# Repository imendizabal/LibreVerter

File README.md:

# Aim of the project
LibreVerter - An open inverter, built for a lifetime. 
A home inverter, to interface battery systems and PV systems with the UK and EU electricity grids.

The LibreVerter will be:
- Durable
- Repairable
- Open-Source

The main goal of the project is to develop an open source inverter (Hardware and Software)  
The initial configuration of the project will be a single phase, 2 kW inverter

An important part of the project is to be able to work with different types of switching components (IGBT/MOSFET). Nowadays, we often see that inverters are replaced after 10 years but they keep working or some faulty inverters that are not easily repared because the design is not modular or easy to fix.

Then, the goal is to design an Open Source inverter that is modular to be easy to be fixed and flexible enough to have differents functionalities (batteries/PV/...)

The project will be divided into different "workpackages" based on the functional blocks needed to make the whole system work. These functional blocks are called "Modules", and may be split into further modules where necessary. The diagram below shows the module definitions we are currently working to. 

1. Supervisory control: development of the main control board able to get the measurements, generate references, ... This board embeds the main mcu.
2. Inverter Board.
3. DC/DC converter: Able to take a variable DC input (48V +/- 20%) and output a stable DC output controllable between 360 V and 500 V.
4. DC Link: A DC link capable of self-protection.
5. A DC filter for smooth input/output.
6. DC Protections for over-current, over-voltage protection and under-voltage protection. 
7. DC connections for physically connecting the DC source to LibreVerter.
8. Maximum Power Point Tracker DC/DC converter for connecting the solar panels to LibreVerter and extracting the maximum power.
9.  AC filter for smooth sine wave input/output.
10. AC protection for over-current and over-voltage protection. Required for compatibility with grid codes.
11. Connections for phsyically conecting the external electrical system to LibreVerter.
12. Human Machine Interface (HMI) to act as the interface between the user and the supervisory control

For the Inverter board, two sub-modules are assumed:
1. Control and Driver board: interface between the supervisory control board and power switch (IGBT's/Mosfet's). The driver board needs to generate the PWM signals based on a reference from the supervisor.
2. Power circuit: power circuit of the inverter

# Who are we making this for?
Our ideal customer profile is:
A “solar as a service” provider. Responsible for through life maintenance. Because:
1. They are able to buy LibreVerters via individual customer orders.
2. Their interests are aligned with selling as many systems as possible, as well as being able to maintain the systems at low cost. Repair and re-use are essential.
3. They are regularly buying inverter systems.
4. They are likely to be a relatively small company, maybe 10-50 people, with big buying power via their customers.

We are also interested in serving other customers who want an inverter for life; we'd love to hear from you if you fit that description! 

# Expected functionalities

- Being able (and allowed) to be connected to the European grid
- MPPT for solar panels (with DC/DC)
- Battery connection
- Communication capabilities (serial,...)
- Working in islanding mode (offgrid)

# 1. Supervisory control board:

For the supervisory control, the firmware on the main mcu should have (main mcu based on STM32G434):

1. Low level drivers
2. Basics functionalities (bootloader, debug uart, pll,...)
3. Advanced functionalities (power management, MPPT, state machine)

The main control board will be able to measure:
1.  3AC voltages (max 400V) - ADC min 14bits
2.  2DC voltages (max 1500V) -ADC min 14bits
3.  4AC/DC current measurement - ADC min 14bits
4.  Temperature measurement

The main control board will have the following interface:
1.  2X UART(1X to RS485; 1X to USB)
2.  1xSPI
3.  2xI2C
4.  1xCAN
5.  6X PWM's
6.  6X DO's
7.  6X DI's
8.  6X AI'S (temp from IGBT/Mos)

Other functions:
1.  Debug LED
2.  RTC (supercap based)
3.  Additionnal ROM (TBD)
4.  Watchdog
5.  Power supply for IGBT's/Mosfets

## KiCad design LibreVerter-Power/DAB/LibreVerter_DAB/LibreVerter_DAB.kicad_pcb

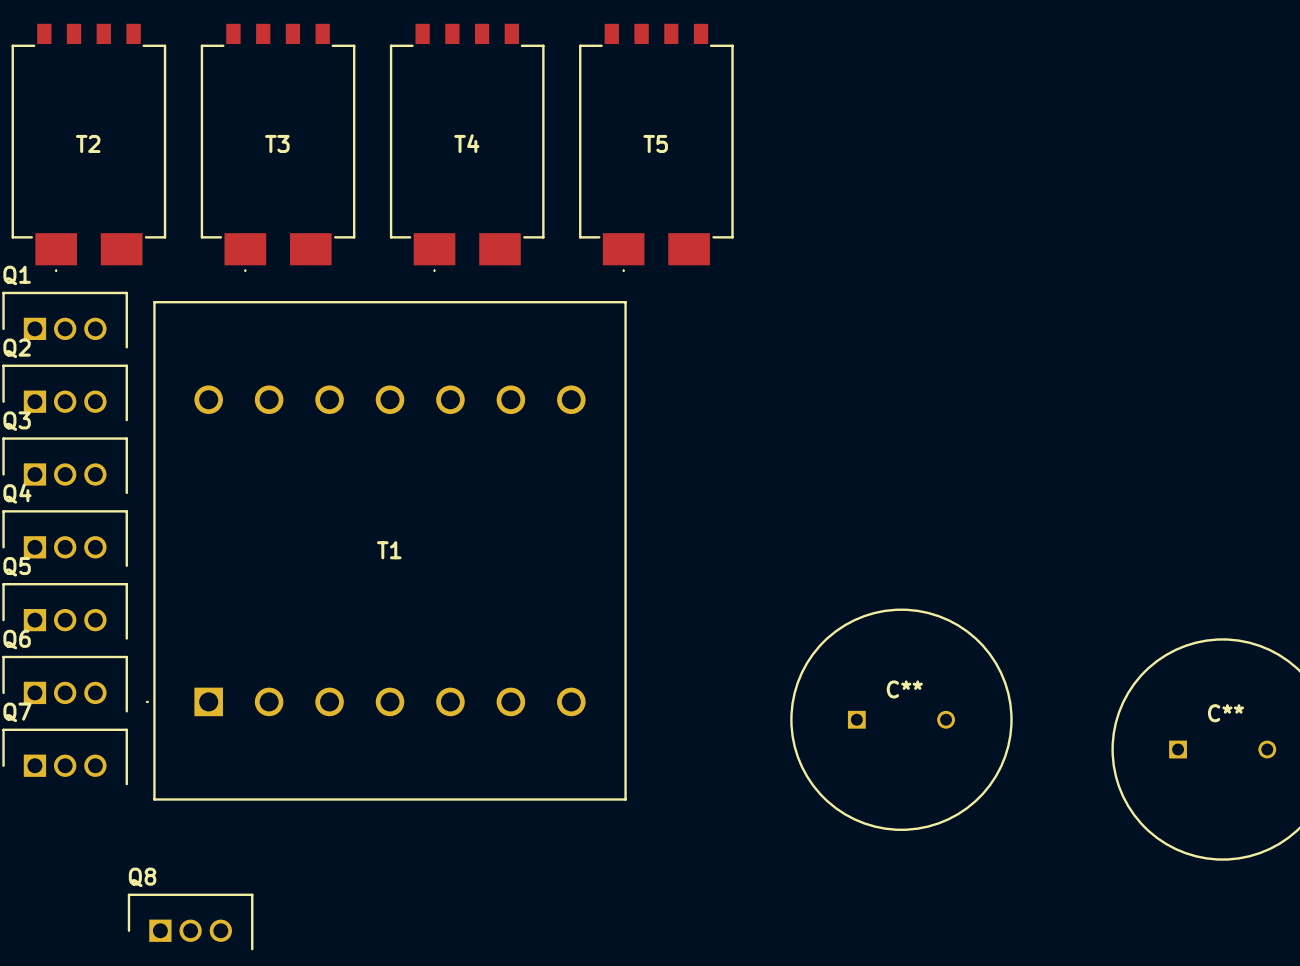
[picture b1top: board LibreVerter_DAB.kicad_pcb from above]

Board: 2 copper layers, 15 parts (0 on the bottom side), 11 nets, no tracks yet.

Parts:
C**: CAPPRD750W80D1850H4200
C**#2: CAPPRD750W80D1850H4200
Q1, Q2, Q3, Q4: IPP023N10N5XKSA1; TO254P457X1003X2115-3P
Q5, Q6, Q7, Q8: IPP60R060P7XKSA1; TO254P457X1003X2115-3P
T1: B66362W1014T001
T2, T3, T4, T5: PAS6322.150NLT; PAS6322150NLT

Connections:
GND: T2.2 (PRI_50KHZ-1MHZ), T5.2 (PRI_50KHZ-1MHZ)
GND2: T3.2 (PRI_50KHZ-1MHZ), T4.2 (PRI_50KHZ-1MHZ)
unnamed: Q1.2 (D), Q3.2 (D)
unnamed: Q1.3 (S), Q2.2 (D), T1.1, T1.2, T1.3
unnamed: Q2.3 (S), T5.1 (PRI_50KHZ-1MHZ)
unnamed: Q3.3 (S), Q4.2 (D), T1.5, T1.6, T1.7
unnamed: Q4.3 (S), T2.1 (PRI_50KHZ-1MHZ)
unnamed: Q5.3 (S), Q6.2 (D), T1.12, T1.13, T1.14
unnamed: Q6.3 (S), T3.1 (PRI_50KHZ-1MHZ)
unnamed: Q7.3 (S), Q8.2 (D), T1.8, T1.9, T1.10
unnamed: Q8.3 (S), T4.1 (PRI_50KHZ-1MHZ)

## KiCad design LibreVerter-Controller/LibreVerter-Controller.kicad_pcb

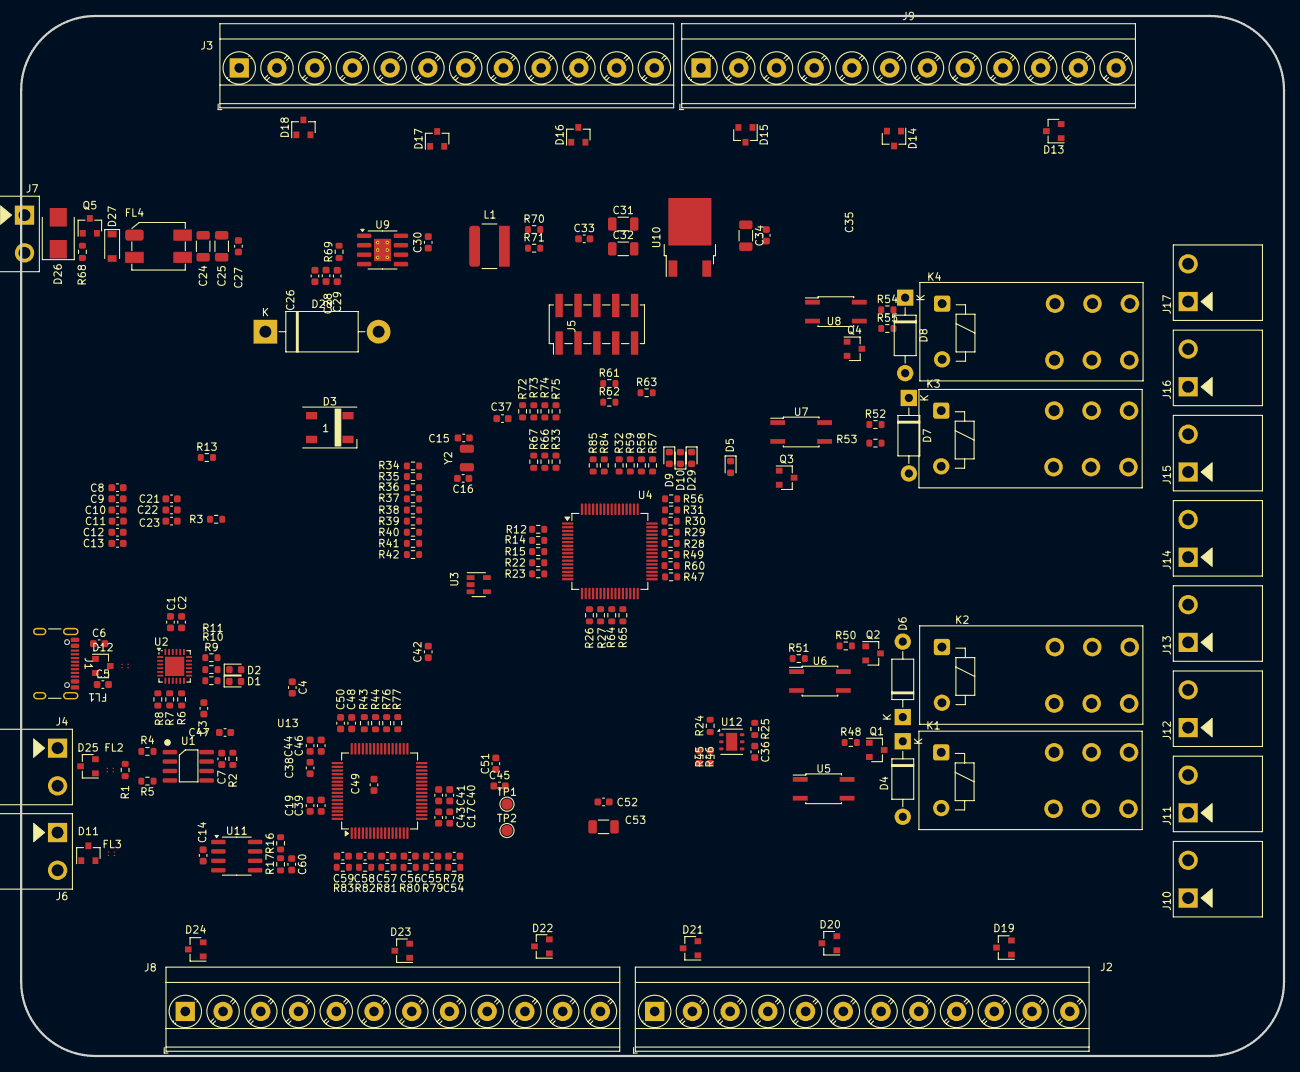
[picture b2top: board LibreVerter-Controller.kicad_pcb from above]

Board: 2 copper layers, 170.0 x 140.0 mm, 215 parts (0 on the bottom side), 174 nets, no tracks yet.

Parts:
C1, C3, C5, C7, C8, C10, C11, C12, C13, C14, C21, C22, C23, C27, C30, C33, C35, C36, C37, C39, C41, C43, C46, C49, C50, C52: 100nF; C_0603_1608Metric
C2, C4, C6, C17, C19, C38, C40, C42, C44, C45, C47, C48, C51: 1uF; C_0603_1608Metric
C9: 10nF; C_0603_1608Metric
C15, C16: 9pF; C_0603_1608Metric
C24, C25: 10uF; C_1206_3216Metric
C26: 22nF; C_0603_1608Metric
C28: 47pF; C_0603_1608Metric
C29, C60: 4.7nF; C_0603_1608Metric
C31, C32, C34: 47uF; C_1206_3216Metric
C53: 22uF; C_1206_3216Metric
C54, C55, C56, C57, C58, C59: 1nF; C_0603_1608Metric
D1, D2: LED_Small; LED_0603_1608Metric
D3: WS2812B; LED_WS2812B_PLCC4_5.0x5.0mm_P3.2mm
D4, D6, D7, D8: 1N47xxA; D_DO-41_SOD81_P10.16mm_Horizontal
D5, D9, D10, D29: 150060RS55040; LED_0603_1608Metric
D11, D25: TVS_2-Channel-7V; SOT-23
D12: 824022; SOT-23
D13, D14, D15, D16, D17, D18, D19, D20, D21, D22, D23, D24: PESD3V3L2BT; SOT-23
D26: SMBJ30CA; D_SMB
D27: Zener_6V; D_SOD-123
D28: 1N5820; D_DO-201AD_P15.24mm_Horizontal
FL1, FL2, FL3: TCM0403M-350-2P-T210; Choke_TDK_TCM0403M-350-2P-T210
FL4: ACM7060-701-2PL-TL01; ChokeSMD_ACM7060
J1: USB_C_Receptacle_USB2.0; USB_C_Receptacle_GCT_USB4105-xx-A_16P_TopMnt_Horizontal
J2, J3, J8, J9: TerminalBlock_1x12; TerminalBlock_Phoenix_MKDS-3-12-5.08_1x12_P5.08mm_Horizontal
J4, J6, J7, J10, J11, J12, J13, J14, J15, J16, J17: 1x02; WURTH-691312510002
J5: Conn_ARM_JTAG_SWD_10; PinHeader_2x05_P2.54mm_Vertical_SMD
K1, K2, K3, K4: RZH3-1C4-D012; Relay_TE_RZH3-1C04-D012
L1: 10μH-5A; Inductor_Wurth_XHMI-6060
Q1, Q2, Q3, Q4: MMSS8050-H-TP; SOT-23
Q5: SI2347DS-T1-GE3; SOT-23
R1, R48, R49, R50, R51, R52, R53, R54, R55, R72, R73, R74: 120Ω; R_0603_1608Metric
R2, R3, R45, R46: 0; R_0603_1608Metric
R4, R5, R14, R15, R22, R23, R26, R27, R28, R29, R30, R31, R32, R33, R34, R35, R36, R37, R38, R39, R40, R41, R42, R47, R56, R57, R58, R59, R60, R61, R62, R63, R64, R65, R66, R67, R84, R85: 100; R_0603_1608Metric
R6: 22K1; R_0603_1608Metric
R7: 47K5; R_0603_1608Metric
R8, R78, R79, R80, R81, R82, R83: 1K; R_0603_1608Metric
R9, R10: 470Ω; R_0603_1608Metric
R11, R13, R43, R44, R76, R77: 10KΩ; R_0603_1608Metric
R12, R24, R25: 4K7; R_0603_1608Metric
R16, R17: 60Ω; R_0603_1608Metric
R68: 12K; R_0603_1608Metric
R69: 49.9; R_0603_1608Metric
R70: 43KΩ; R_0603_1608Metric
R71: 8.2KΩ; R_0603_1608Metric
R75: 330; R_0603_1608Metric
TP1, TP2: TestPoint_1.5mm; TestPoint_Pad_D1.5mm
U1: SP3485EN; SOIC-8_3.9x4.9mm_P1.27mm
U2: CP2102N-A02-GQFN24; QFN-24-1EP_4x4mm_P0.5mm_EP2.6x2.6mm
U3: STWD100; SOT-23-5
U4, U13: LQFP-64_10x10mm_P0.5mm
U5, U6, U7, U8: LTV-356T; SO-4_4.4x3.6mm_P2.54mm
U9: TPS54331DR; SOIC-8-1EP_3.9x4.9mm_P1.27mm_EP2.29x3mm_ThermalVias
U10: BD33FC0FP-E2; TO-252-2
U11: ATA6560; SOIC-8_3.9x4.9mm_P1.27mm
U12: HDC2080; Texas_PWSON-N6
Y2: Crystal; Oscillator_SMD_ECS_2520MV-xxx-xx-4Pin_2.5x2.0mm

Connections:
+3V3: C1.1, C2.1, C8.1, C11.1, C12.1, C13.1, C14.1, C21.1, C22.1, C23.1, C34.1, C35.1, C36.1, C44.1, C46.1, C48.1, C50.1, D1.2 (K), D2.2 (K), J5.1 (VTref), R2.1, R8.1, R13.2, R24.2, R25.1, R45.1, R74.1, U2.5 (VIO), U2.6 (VDD), U2.7 (VREGIN), U3.5 (VCC), U4.16 (VDD), U4.29 (VDDA), U4.32 (VDD), U4.48 (VDD), U4.64 (VDD), U10.3 (Vout), U11.3 (VCC), U12.5 (VDD), U13.48 (DVDD), U13.50 (DVDD)
+5V: C17.1, C19.1, C31.1, C32.1, C33.1, C37.1, C38.1, C39.1, C40.1, C41.1, C42.1, C43.1, D3.4 (VDD), L1.2, R3.1, R70.1, R75.1, U10.1 (Vin), U13.19 (AVDD), U13.21 (AVDD), U13.22 (AVDD), U13.54 (AVDD1), U13.56 (AVDD), U13.59 (AVDD)
+BATT: C10.1, U4.1 (VBAT)
/CAN_N: FL3.4, R17.2, U11.6 (CANL)
/CAN_P: FL3.2, R16.1, U11.7 (CANH)
/Dry Contact_1/DRY1_C: J11.2, K1.12
/Dry Contact_1/DRY1_O: J11.1, K1.14
/Dry Contact_1/DRY_CONT: J10.2, K1.11
/Dry Contact_1/DRY_V: D4.1 (K), J10.1, K1.A2, U5.4
/Dry Contact_2/DRY1_C: J12.2, K2.12
/Dry Contact_2/DRY1_O: J12.1, K2.14
/Dry Contact_2/DRY_CONT: J13.2, K2.11
/Dry Contact_2/DRY_V: D6.1 (K), J13.1, K2.A2, U6.4
/Dry Contact_3/DRY1_C: J15.2, K3.12
/Dry Contact_3/DRY1_O: J15.1, K3.14
/Dry Contact_3/DRY_CONT: J14.2, K3.11
/Dry Contact_3/DRY_V: D7.1 (K), J14.1, K3.A2, U7.4
/Dry Contact_4/DRY1_C: J17.2, K4.12
/Dry Contact_4/DRY1_O: J17.1, K4.14
/Dry Contact_4/DRY_CONT: J16.2, K4.11
/Dry Contact_4/DRY_V: D8.1 (K), J16.1, K4.A2, U8.4
/EXT_CAN_N: D11.2, FL3.3, J6.2
/EXT_CAN_P: D11.1, FL3.1, J6.1
/IN_AN1: D24.3, J8.1, R78.1
/IN_AN2: D24.1, J8.3, R79.1
/IN_AN3: D19.1, D23.3, J2.12 (Pin_8), J8.5, R33.1, R80.1
/IN_AN4: D23.1, J8.7 (Pin_10), R81.1
/IN_AN5: D22.3, J8.9 (Pin_12), R82.1
/IN_AN6: D22.1, J8.12 (Pin_8), R83.1
/IN_DIG1: D21.3, J2.1, R28.1
/IN_DIG2: D21.1, J2.3, R29.1
/IN_DIG3: D20.3, J2.5, R30.1
/IN_DIG4: D20.1, J2.7 (Pin_10), R31.1
/IN_DIG5: D19.3, J2.9 (Pin_12), R32.1
/JTCK: J5.4 (SWDCLK/TCK), R58.1
/JTDI: J5.8 (NC/TDI), R59.1
/JTDO: J5.6 (SWO/TDO), R66.2, R67.2
/JTMS: J5.2 (SWDIO/TMS), R57.1
/MCU/CAN_NSIL: R85.2, U11.5 (NSIL)
/MCU/CAN_STBY: R84.2, U11.8 (STBY)
/MCU/LED1: R72.1, U4.55 (PD2)
/MCU/LED2: R73.1, U4.30 (PB10)
/MCU/MCU_RST: C9.2, R12.2, R13.1, U4.7 (NRST)
/MCU/RS485: U1.2 (~RE), U1.3 (DE), U2.12 (RS485/IO2)
/MCU/RX0_3V3: R4.1, U2.21 (TXD)
/MCU/SCL: R25.2, U12.6 (SCL)
/MCU/SDA: R24.1, U12.1 (SDA)
/MCU/TX0_3V3: R5.1, U2.20 (RXD)
/MCU/VCAP2: C51.1, C52.1, U13.30 (VCAP2)
/MCU/VCAP3: C47.1, C49.1, U13.55 (VCAP3)
/MCU/VCAP4: C45.1, U13.26 (VCAP4)
/OUT_DIG1: D18.3, J3.1, R14.1
/OUT_DIG2: D18.1, J3.3, R15.1
/OUT_DIG3: D17.3, J3.5, R22.1
/OUT_DIG4: D17.1, J3.7 (Pin_10), R23.1
/OUT_DIG5: D16.3, J3.9 (Pin_12), R26.1
/OUT_DIG6: D16.1, J3.12 (Pin_8), R27.1
/OUT_DRY1: R49.2, R60.2
/OUT_DRY2: R51.2, R61.2
/OUT_DRY3: R53.2, R62.2
/OUT_DRY4: R55.2, R63.2
/OUT_PWM1: D15.3, J9.1, R34.1
/OUT_PWM2: D15.1, J9.3, R35.1
/OUT_PWM3: D14.3, J9.5, R36.1
/OUT_PWM4: D14.1, J9.7 (Pin_10), R37.1
/OUT_PWM5: D13.3, J9.9 (Pin_12), R38.1
/OUT_PWM6: D13.1, J9.12 (Pin_8), R56.1
/RS485_EXT_N: D25.1, FL2.3, J4.2
/RS485_EXT_P: D25.2, FL2.1, J4.1
/RS485_N: FL2.4, R1.2, U1.7 (B)
/RS485_P: FL2.2, R1.1, U1.6 (A)
/USB_D_N: FL1.4, U2.4 (D-)
/USB_D_P: FL1.2, U2.3 (D+)
/USB_IN_N: D12.1 (IO1), FL1.3, J1.A6 (D+), J1.B6 (D+)
/USB_IN_P: D12.3 (IO2), FL1.1, J1.A7 (D-), J1.B7 (D-)
GND: C1.2, C2.2, C3.2, C4.2, C5.2, C6.2, C7.2, C8.2, C9.1, C10.2, C11.2, C12.2, C13.2, C14.2, C15.2, C16.2, C17.2, C19.2, C21.2, C22.2, C23.2, C26.2, C28.2, C31.2, C32.2, C33.2, C34.2, C35.2, C36.2, C37.2, C38.2, C39.2, C40.2, C41.2, C42.2, C43.2, C44.2, C45.2, C46.2, C47.2, C48.2, C49.2, C50.2, C51.2, C52.2, C53.2, C54.2, C55.2, C56.2, C57.2, C58.2, C59.2, C60.1, D3.2 (GND), D5.2 (K), D9.2 (K), D10.2 (K), D11.3, D12.2 (GND), D13.2, D14.2, D15.2, D16.2, D17.2, D18.2, D19.2, D20.2, D21.2, D22.2, D23.2, D24.2, D25.3, D28.2 (A), D29.2 (K), J1.A1 (GND), J1.A12 (GND), J1.B1 (GND), J1.B12 (GND), J1.S1 (SHIELD), J2.2, J2.4, J2.6, J2.8 (Pin_11), J2.10 (Pin_13), J2.11 (Pin_7), J3.2, J3.4, J3.6, J3.8 (Pin_11), J3.10 (Pin_13), J3.11 (Pin_7), J5.3 (GND), J5.5 (GND), J5.9 (GNDDetect), J8.2, J8.4, J8.6, J8.8 (Pin_11), J8.10 (Pin_13), J8.11 (Pin_7), J9.2, J9.4, J9.6, J9.8 (Pin_11), J9.10 (Pin_13), J9.11 (Pin_7), R7.2, R11.2, R43.2, R44.2, R46.2, R69.2, R71.2, R76.2, R77.2, U1.5 (GND), U2.2 (GND), U2.25 (GND), U3.2 (GND), U4.15 (VSS), U4.27 (VSSA), U4.31 (VSS), U4.47 (VSS), U4.63 (VSS), U5.2, U6.2, U7.2, U8.2, U9.7 (GND), U9.9 (PAD), U10.2 (GND), U11.2 (GND), U12.2 (GND), U13.1 (IN8N), U13.2 (IN8P), U13.3 (IN7N), U13.4 (IN7P), U13.5 (IN6N), U13.7 (IN5N), U13.9 (IN4N), U13.11 (IN3N), U13.13 (IN2N), U13.15 (IN1N), U13.20 (AVSS), U13.23 (AVSS), U13.27 (REFN), U13.32 (AVSS), U13.33 (DGND), U13.49 (DGND), U13.51 (DGND), U13.53 (AVSS1), U13.57 (AVSS), U13.58 (AVSS)
GND1: Q1.2 (E), Q2.2 (E), Q3.2 (E), Q4.2 (E)
unnamed: C24.2, C25.2, C27.2, FL4.3
unnamed: C29.2, R69.1
unnamed: C60.2, R16.2, R17.1
unnamed: D1.1 (A), R9.2
unnamed: D2.1 (A), R10.2
unnamed: D4.2 (A), K1.A1, Q1.3 (C)
unnamed: D5.1 (A), R72.2
unnamed: D6.2 (A), K2.A1, Q2.3 (C)
unnamed: D7.2 (A), K3.A1, Q3.3 (C)
unnamed: D8.2 (A), K4.A1, Q4.3 (C)
unnamed: D9.1 (A), R73.2
unnamed: D10.1 (A), R74.2
unnamed: D26.1 (A1), FL4.2, J7.2, R68.1
unnamed: D26.2 (A2), J7.1, Q5.3 (D)
unnamed: D27.2 (A), Q5.1 (G), R68.2
unnamed: D27.1 (K), FL4.1, Q5.2 (S)
unnamed: C30.2, D28.1 (K), L1.1, U9.8 (PH)
unnamed: D29.1 (A), R75.2
unnamed: Q1.1 (B), R48.1
unnamed: Q2.1 (B), R50.1
unnamed: Q3.1 (B), R52.1
unnamed: Q4.1 (B), R54.1
unnamed: R48.2, U5.3
unnamed: R49.1, U5.1
unnamed: R50.2, U6.3
unnamed: R51.1, U6.1
unnamed: R52.2, U7.3
unnamed: R53.1, U7.1
unnamed: R54.2, U8.3
unnamed: R55.1, U8.1
unnamed: R5.2, U1.4 (DI)
unnamed: R4.2, U1.1 (RO)
unnamed: C7.1, R2.2, R3.2, U1.8 (VCC)
unnamed: R9.1, U2.13 (RXT/IO1)
unnamed: R10.1, U2.14 (TXT/IO0)
unnamed: R6.2, R7.1, U2.8 (VBUS)
unnamed: R8.2, U2.9 (~RST)
unnamed: R11.1, U2.15 (~SUSPEND)
unnamed: R12.1, U3.1 (~WDO)
unnamed: C16.1, U4.3 (OSC32_IN), Y2.1
unnamed: C15.1, U4.4 (OSC32_OUT), Y2.2
unnamed: R34.2, U4.12 (PA0)
unnamed: R35.2, U4.13 (PA1)
unnamed: R36.2, U4.14 (PA2)
unnamed: R37.2, U4.17 (PA3)
unnamed: R38.2, U4.18 (PA4)
unnamed: R39.2, U4.19 (PA5)
unnamed: R40.2, U4.20 (PA6)
unnamed: R41.2, U4.21 (PA7)
unnamed: R42.2, U4.42 (PA8)
unnamed: R47.2, U4.43 (PA9)
unnamed: R56.2, U4.46 (PA12)
unnamed: R57.2, U4.49 (PA13)
unnamed: R58.2, U4.50 (PA14)
unnamed: R59.2, U4.51 (PA15)
unnamed: R64.1, U4.24 (PB0)
unnamed: R65.1, U4.25 (PB1)
unnamed: R66.1, U4.56 (PB3)
unnamed: R67.1, U4.57 (PB4)
unnamed: R84.1, U4.58 (PB5)
unnamed: R85.1, U4.59 (PB6)
unnamed: R60.1, U4.33 (PB11)
unnamed: R61.1, U4.34 (PB12)
unnamed: R62.1, U4.35 (PB13)
unnamed: R63.1, U4.36 (PB14)
unnamed: R14.2, U4.8 (PC0)
unnamed: R15.2, U4.9 (PC1)
unnamed: R22.2, U4.10 (PC2)
unnamed: R23.2, U4.11 (PC3)
unnamed: R26.2, U4.22 (PC4)
unnamed: R27.2, U4.23 (PC5)
unnamed: R28.2, U4.38 (PC6)
unnamed: R29.2, U4.39 (PC7)
unnamed: R30.2, U4.40 (PC8)
unnamed: R31.2, U4.41 (PC9)
unnamed: R32.2, U4.52 (PC10)
unnamed: R33.2, U4.53 (PC11)
unnamed: C30.1, U9.1 (BOOT)
unnamed: C28.1, C29.1, U9.6 (COMP)
unnamed: C26.1, U9.4 (SS)
unnamed: C24.1, C25.1, C27.1, FL4.4, U9.2 (VIN)
unnamed: R70.2, R71.1, U9.5 (VSENSE)
unnamed: R45.2, R46.1, U12.3 (ADDR)
unnamed: R77.1, U13.42 (GPIO1)
unnamed: R76.1, U13.44 (GPIO2)
unnamed: R44.1, U13.45 (GPIO3)
unnamed: R43.1, U13.46 (GPIO4)
unnamed: C54.1, R78.2, U13.16 (IN1P)
unnamed: C55.1, R79.2, U13.14 (IN2P)
unnamed: C56.1, R80.2, U13.12 (IN3P)
unnamed: C57.1, R81.2, U13.10 (IN4P)
unnamed: C58.1, R82.2, U13.8 (IN5P)
unnamed: C59.1, R83.2, U13.6 (IN6P)
unnamed: TP1.1, U13.18 (TESTN)
unnamed: TP2.1, U13.17 (TESTP)
unnamed: C53.1, U13.28 (VCAP1)
VBUS: C3.1, C4.1, C5.1, C6.1, J1.A4 (VBUS), J1.A9 (VBUS), J1.B4 (VBUS), J1.B9 (VBUS), R6.1

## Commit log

2025-11-04 Inverter in voltage control mode 1 kW output
    Inverter stage in a "good enough" state to build the DC-DC stage.
    The inverter is operating in a simple closed-loop voltage control mode using PID control.
    The interfaces are setup so that the gate driver is on the control board and is expecting a current reference. Note that this current reference does not work yet!
2025-11-04 DC-DC Stage simulation runs but doesn't work
    DC-DC stage simulation has all of the components needed to work but outputs nothing useful.
2025-11-04 Working simple voltage control DAB
    Working simple voltage control DAB
    Interfaces in place for controller development and component sizing.
    Separation of gate driver needs copying over to the DC-AC section.
2025-11-04 Minor changes and screenshots
2025-11-19 Added Stevie's slides / notes
2025-12-09 Iterated DAB to 5 kW variant
2025-12-09 Started a prototyping bill of materials
2025-12-12 Iterated DAB Magnetics design to ETD core
    Iterated DAB magnetics design considering, E, Toroidal and ETD types.
    ETD looks more promising and simplest to implement.
    Downloaded the openmagnetics model direct into the simulation in the "DAB playground".
2025-12-12 DAB playground mods
2025-12-12 DAB BOM update
2025-12-12 Updated BOM
2025-12-15 minor BOM update
2025-12-17 Test update to BOM
2026-01-29 Changed folder names to LibreVerter
2026-01-29 Changed filenames to LibreVerter
2026-01-29 Updated the DAB transformer design for 2 kW peak power
2026-01-29 First draft of DAB schematic
2026-01-29 Updates to DAB schematic
2026-02-10 Updates to LibreVerter SIMBA simulation
    Updates for consistency between different designs in the SIMBA file.
2026-02-10 Minor updates to power board schematic
2026-02-13 DAB board design principles added
2026-02-13 Added TVS diodes to BOM
2026-02-16 Revise project description and goals in README
    Updated wording for project goals and characteristics.
